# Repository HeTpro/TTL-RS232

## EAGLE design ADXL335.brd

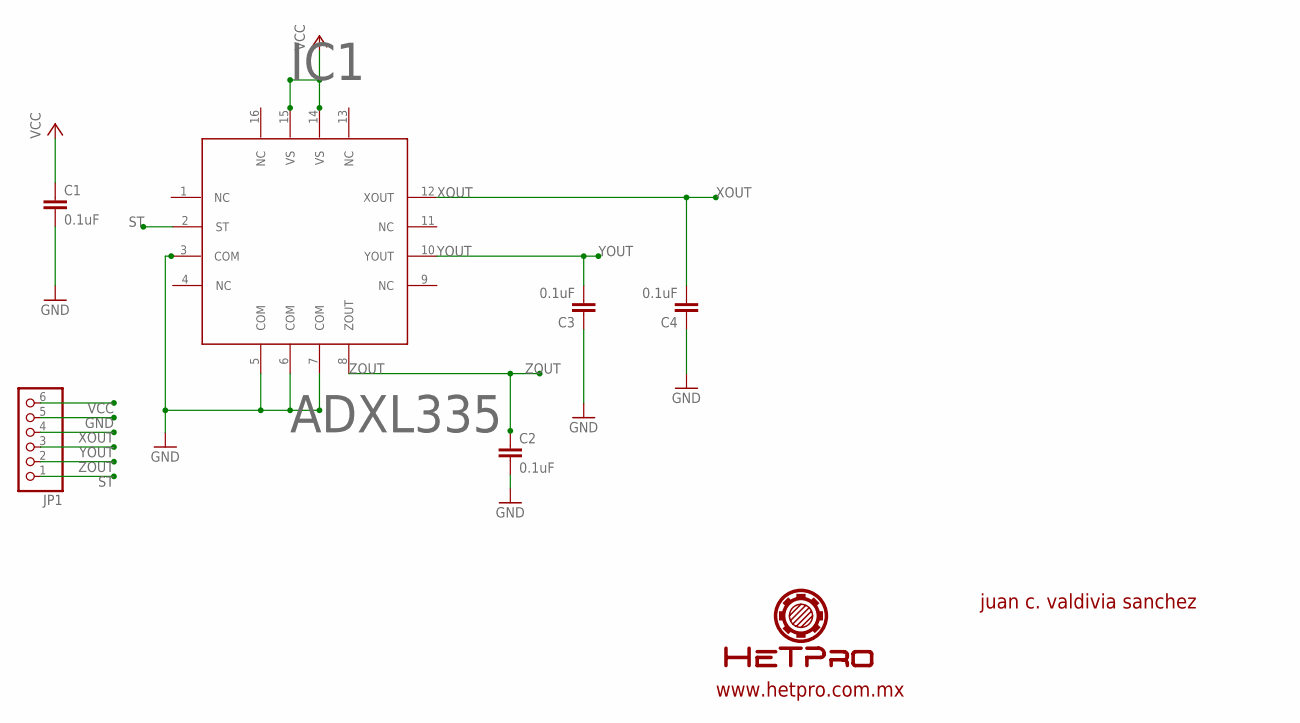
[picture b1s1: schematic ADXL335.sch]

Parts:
C1, C2, C3, C4: 0.1uF; C0603
IC1: ADXL335
JP1: PINHD-1X6; 1X06

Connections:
GND: C1.2, C2.2, C3.1, C4.1, IC1.3 (COM), IC1.5 (COM), IC1.6 (COM), IC1.7 (COM), JP1.5
ST: IC1.2 (ST), JP1.1
VCC: C1.1, IC1.14 (VS), IC1.15 (VS), JP1.6
XOUT: C4.2, IC1.12 (XOUT), JP1.4
YOUT: C3.2, IC1.10 (YOUT), JP1.3
ZOUT: C2.1, IC1.8 (ZOUT), JP1.2

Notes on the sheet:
juan c. valdivia sanchez
www.hetpro.com.mx

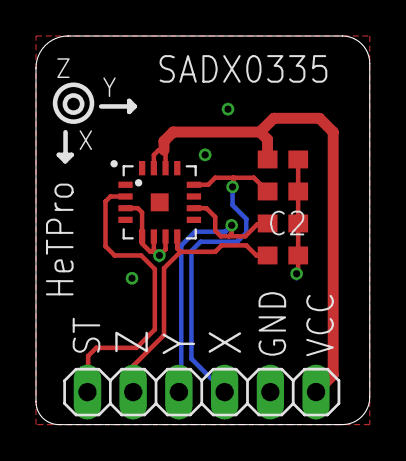
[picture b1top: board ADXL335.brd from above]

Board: 2 copper layers, 18.5 x 21.6 mm, 6 parts (0 on the bottom side), 6 nets.

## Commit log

2015-04-22 :boom::camel: Added .gitattributes & .gitignore files
2015-04-22 Archivos
